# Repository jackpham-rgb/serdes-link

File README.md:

# serdes-link

A 5 Gb/s serial link, modeled from the transmitter to the recovered bits, with the digital parts rebuilt in SystemVerilog and checked against the model. [Portfolio page](https://jackpham-rgb.github.io/jack-portfolio/)

## Goal and specs

Send 5 billion bits per second down 36 inches of ordinary circuit-board trace and still read every bit correctly at the far end.

That sounds easy until you look at what the trace does. A long trace passes slow changes well and fast changes badly, so each bit smears into the bit slots after it. I learned this smearing has a name, inter-symbol interference, or ISI, and that is what I call it from here on.

The standard way to see ISI is to overlay thousands of received bits on one screen. If the ones and zeros stay apart, there is an open gap in the middle that looks like an eye. That picture is called an eye diagram. A closed eye means the receiver cannot tell a one from a zero.

| Spec | Target | Result |
|---|---|---|
| Bit rate | 5 Gb/s, two-level (NRZ) | 5 Gb/s |
| Channel | 36 in FR4 microstrip, synthetic | 14.9 dB loss at 2.5 GHz |
| Bit error rate | below 1e-12 | below 1e-15 (computed) |
| Eye opening at 1e-12 | open | 126 mV tall, 0.41 of a bit wide |
| Clock offset tolerated | 200 ppm | locks and tracks 200 ppm |
| RTL matches the model | bit for bit | PRBS and clock-recovery filter exact, DFE over 99% of decisions |

## How it works

Each block fixes the smearing in a different way. These are the names engineers use, so I use them too.

- **TX FFE** (feed-forward equalizer). The transmitter sends each bit a little weaker when it repeats the bit before it. This is called de-emphasis. I use the common 3.5 dB setting.
- **CTLE** (continuous-time linear equalizer). An amplifier at the receiver that boosts fast changes more than slow ones, undoing the trace's loss. The amount of boost is called peaking.
- **DFE** (decision-feedback equalizer). Once the receiver has decided a bit, it knows how that bit will smear into the next four, so it subtracts that smear. The four weights are called taps, and they tune themselves with a rule called sign-sign LMS.
- **CDR** (clock and data recovery). The receiver has no clock wire from the transmitter. It watches where the signal crosses zero and steers its own sampling clock to match. Mine is the bang-bang type, which only asks "early or late?" each bit.

Three design decisions mattered most:

1. **Pick a channel that needs the equalizers.** At 12 inches the eye is already open at this speed, so there was nothing to fix. At 36 inches the raw eye is closed.
2. **Measure the eye statistically.** Simulating enough bits to see one error in a trillion is not practical. Instead the model takes the response to one bit, works out every way neighboring bits can add up, and computes the error rate directly. This is called a statistical eye.
3. **Choose CTLE peaking by sweep.** Too little leaves ISI. Too much amplifies noise. The sweep finds the setting with the tallest eye.

## Results

| Step | Eye height at 1e-12 | Eye width at 1e-12 | BER at eye center | Bit errors in simulation |
|---|---|---|---|---|
| Raw channel | 0 mV | 0.00 UI | 2e-02 | 89 of 3700 |
| + TX FFE | 0 mV | 0.00 UI | 5e-07 | 0 of 3700 |
| + CTLE | 115 mV | 0.34 UI | < 1e-15 | 0 of 3700 |
| + DFE | 126 mV | 0.41 UI | < 1e-15 | 0 of 3700 |

UI means unit interval, the time of one bit (200 ps here). BER is bit error rate. The computed error rate for the raw channel (1.9%) agrees with counting errors in the simulated bits (2.4%). The + DFE row uses ideal taps equal to the pulse-response postcursors; the taps that sign-sign LMS actually learns are in the DFE figure below.

The bathtub plot shows error rate against where in the bit the receiver samples. A wider flat bottom means more room for clock error.

In RTL, the PRBS bit generator matches the Python model on all 2000 bits, the clock-recovery loop filter matches on every one of about 4000 steps, and the DFE agrees on over 99% of 4000 decisions. All three run in cocotb with Icarus Verilog.

More detail: [spec](docs/00-spec.md), [link model](docs/01-model.md), [RTL](docs/03-rtl.md), [the math](docs/04-applied-math.md), [supply noise and jitter](docs/05-power-integrity.md).

## What broke and how I fixed it

- **The eye looked closed when it was open.** My eye-height measurement included the dead time before the first bit arrives, so it read zero on an open eye. I caught it when the 12 inch plot plainly showed an open eye next to a number saying closed. The measurement now skips start-up and samples at the eye center.
- **Wrong port order gave a silent zero.** The channel file listed ports in an order the conversion did not expect, and the loss came out as exactly zero with no error. A test against two uncoupled lines caught it.
- **Feedback with the wrong sign.** Both the DFE update and the CDR loop were first written as positive feedback. The DFE tap ran away; the CDR drifted to the edge of the eye from any starting point.
- **A testbench race.** Reading a registered output right after the clock edge returned the old value. Reading after the falling edge fixed it.

## The test board

To check the model against a real trace, I designed a board to measure. It has two 12 in lines, one for each half of the differential pair, and a 1 in line. The short line is called a thru. Measuring it lets me subtract what the connectors add, so only the trace is left. I learned this is called de-embedding.

[Schematic (PDF)](pcb/serdes_test_channel_schematic.pdf), [bill of materials](pcb/serdes_test_channel_bom.csv), and the full design are in [`pcb/`](pcb/).

## Reproduce it

Python 3.10 or newer, plus [Icarus Verilog](https://github.com/steveicarus/iverilog) for the RTL tests.

```bash
python -m venv .venv && source .venv/bin/activate   # .venv\Scripts\activate on Windows
pip install -r requirements.txt
pip install -e .
python -m pytest              # 43 tests; the 3 RTL cosimulations skip without Icarus Verilog
python scripts/run_link.py    # regenerates the figures and results table above
```

## Repo layout

```
src/serdeslink/   the link model: channel, TX, CTLE, DFE, CDR, analysis
scripts/          scripts that produce every figure and number
rtl/              SystemVerilog: PRBS generator, DFE, CDR loop filter
tests/            pytest unit tests and cocotb RTL testbenches
data/touchstone/  the channel S-parameter file and its generator
pcb/              KiCad test board: two 12 in lines and a 1 in thru line
docs/             write-ups, figures, results
```

## Limits and next revision

- The channel is a synthetic model, not a measurement. The test board in `pcb/` is designed and passes design-rule checks but has not been fabricated.
- This is a model plus verified digital blocks. It has not run on an FPGA or silicon.
- The DFE adds little here because the CTLE already removes most of the smear. A lossier channel would show it better.
- Next revision: measure a real trace, and tighten the DFE check to bit-exact with a fixed-point reference model.

## Watch it work

The same bits go down the same trace four times, with one more equalizer switched on each time. On the left, the gray square wave is what was sent and the blue curve is what arrives. Each dot is where the receiver decides 1 or 0, and red dots are wrong reads. On the right, every received bit is stacked on top of the others. The gap in the middle is the eye: the bigger it is, the more room the receiver has before it reads a bit wrong.

Made with `python scripts/make_animation.py`, using the same simulation as the results above.

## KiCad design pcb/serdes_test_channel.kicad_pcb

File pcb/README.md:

# Test channel board

A KiCad board for measuring a real channel with a network analyzer (VNA), so a measured S-parameter file can replace the synthetic one in `data/touchstone/`. It is designed and passes all checks; it has not been fabricated or measured.

Each line is 12 inches. The link model uses 36 inches, which three lines in series would give, or the 12 inch measurement can be scaled in loss per inch.

## What is on the board

| Item | Detail |
|---|---|
| Two 12 inch lines | 50 ohm microstrip on F.Cu, pad center to pad center, 20 mm apart. They are the physical version of the two uncoupled lines (TX+ to RX+, TX- to RX-) in `make_synthetic_channel.py`. Ports: J1 TX+, J2 TX-, J3 RX+, J4 RX-, the same order the model uses. |
| 1 inch thru | J5 to J6, with identical connectors and launches. Measuring it gives the connector and launch response, which can be de-embedded from the 12 inch results. |
| Connectors | Six Amphenol 132289 edge-launch SMA connectors. |
| Stackup | 4 layers, 1.6 mm. F.Cu carries the lines, In1.Cu is a solid ground reference, In2.Cu and B.Cu are ground. |
| Launch | Each line tapers from the 1.5 mm connector pad to the trace over 3 mm. In1.Cu is cleared under the pad and taper, so the wide pad does not load the launch. |
| Shielding | A row of ground vias 1.2 mm from each side of every line, every 2 mm. |

The schematic is `serdes_test_channel.kicad_sch` ([PDF](serdes_test_channel_schematic.pdf)). It is six coaxial
connectors joined by three nets: `CH_P` (J1 to J3), `CH_M` (J2 to J4) and
`THRU` (J5 to J6).

## Impedance

The trace is 0.16 mm wide. With about 0.1 mm of prepreg (er near 4.05)
between F.Cu and In1.Cu, the Hammerstad-Jensen microstrip formula gives about
50.6 ohms. Prepreg thickness and dielectric constant vary by fab and stackup,
so confirm the width with the fab's impedance calculator before ordering. The
board specifies a controlled-impedance stackup for that reason.

## Checks

| Check | Result |
|---|---|
| KiCad design rule check | 0 violations, 0 unconnected items |
| Schematic electrical rules check | 0 errors, 0 warnings |

The copper-to-edge clearance rule is set to ignore in
`serdes_test_channel.kicad_pro`, because edge-launch pads and the ground
pours reach the board edge on purpose.

## Files

| File | What it is |
|---|---|
| `serdes_test_channel.kicad_pro`, `.kicad_sch`, `.kicad_pcb` | KiCad project, schematic and board |
| `serdes_test_channel_gerbers.zip` | Gerbers and drill file for a fab |
| `serdes_test_channel_schematic.pdf` | Schematic as a PDF |
| `serdes_test_channel_bom.csv` | Parts list: six Amphenol 132289 edge-launch SMA connectors |
| `make_test_channel_pcb.py`, `make_schematic.py` | Scripts that generate the board and schematic, run with KiCad's bundled Python |
| `img/` | Schematic and 3D render |

To regenerate:

```bash
"C:/Program Files/KiCad/10.0/bin/python.exe" pcb/make_test_channel_pcb.py
"C:/Program Files/KiCad/10.0/bin/python.exe" pcb/make_schematic.py
```

## Measuring it

1. Confirm the trace width with the fab's calculator and order a small run.
2. Measure the thru and both 12 inch lines with a VNA (SOLT calibrated at the
   cable ends).
3. Save the 4-port result as a Touchstone file in `data/touchstone/` and
   point `channel.load()` at it. No code changes are needed.

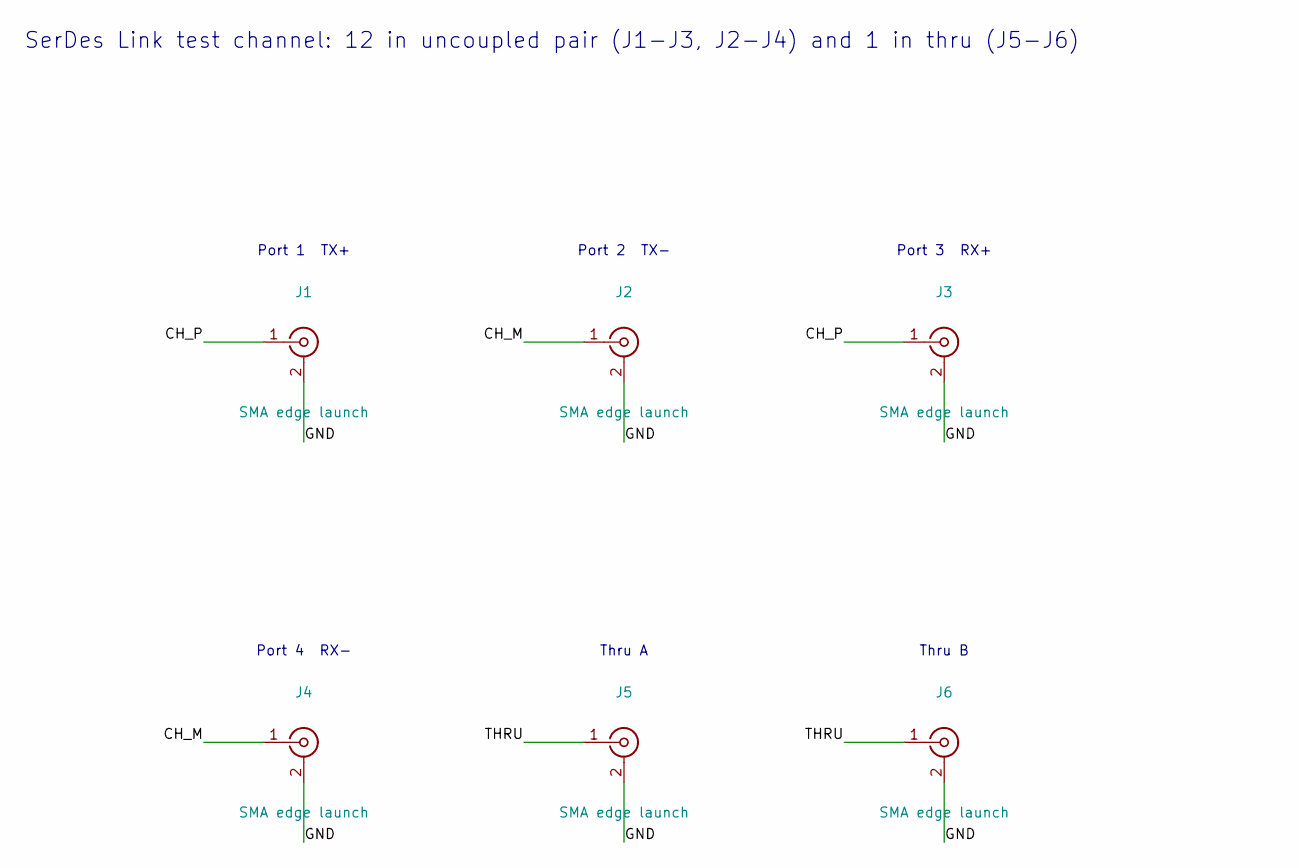
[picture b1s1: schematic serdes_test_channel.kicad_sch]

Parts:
J1, J2, J3, J4, J5, J6: SMA edge launch; SMA_Amphenol_132289_EdgeMount

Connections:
CH_M: J2.1 (In), J4.1 (In)
CH_P: J1.1 (In), J3.1 (In)
GND: J1.2 (Ext), J2.2 (Ext), J3.2 (Ext), J4.2 (Ext), J5.2 (Ext), J6.2 (Ext)
THRU: J5.1 (In), J6.1 (In)

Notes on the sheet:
Port 1 TX+
Port 2 TX-
Port 3 RX+
Port 4 RX-
Thru A
Thru B
SerDes Link test channel: 12 in uncoupled pair (J1-J3, J2-J4) and 1 in thru (J5-J6)

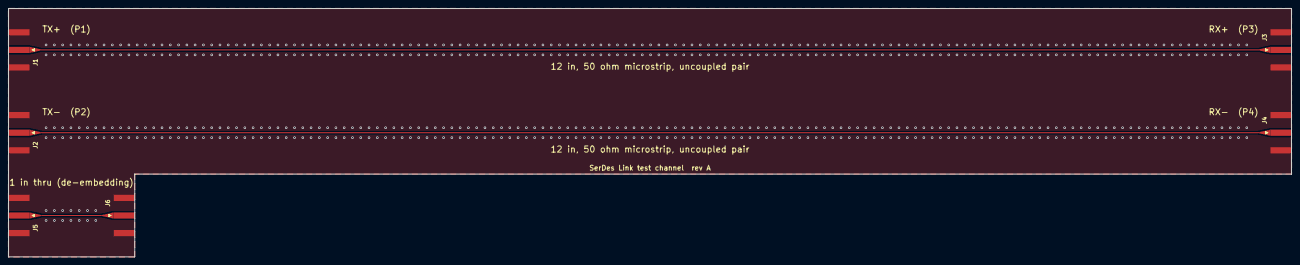
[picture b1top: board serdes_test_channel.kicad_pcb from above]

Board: 4 copper layers, 309.9 x 60.0 mm, 6 parts (0 on the bottom side), 4 nets.
